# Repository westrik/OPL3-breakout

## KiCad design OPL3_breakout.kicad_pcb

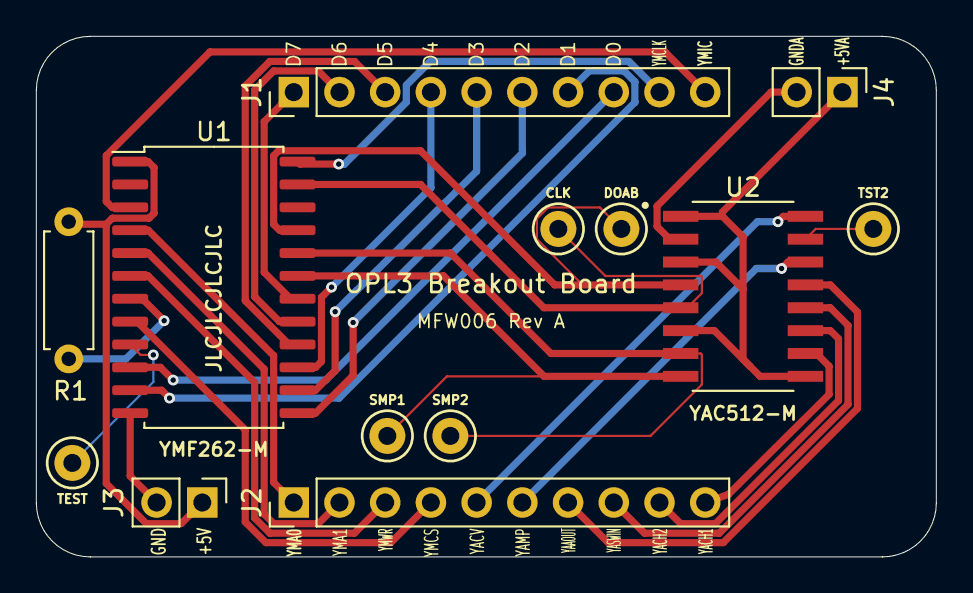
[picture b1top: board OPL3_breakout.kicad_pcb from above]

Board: 4 copper layers, 50.0 x 28.9 mm, 13 parts (0 on the bottom side), 31 nets.

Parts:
J1, J2: Conn_01x10; PinHeader_1x10_P2.54mm_Vertical
J3, J4: Conn_01x02; PinHeader_1x02_P2.54mm_Vertical
R1: 10K; R_Axial_DIN0207_L6.3mm_D2.5mm_P7.62mm_Horizontal
TP1: DOAB; TestPoint_Keystone_5000-5004_Miniature
TP2: CLK; TestPoint_Keystone_5000-5004_Miniature
TP3: TST2; TestPoint_Keystone_5000-5004_Miniature
TP4: TEST; TestPoint_Keystone_5000-5004_Miniature
TP5: SMP2; TestPoint_Keystone_5000-5004_Miniature
TP6: SMP1; TestPoint_Keystone_5000-5004_Miniature
U1: YMF262-M; SOP-24_7.5x15.4mm_P1.27mm
U2: YAC512-M; SOP127P780X200-16N

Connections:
+5V: J3.1, R1.1, U1.1
+5VA: J4.1, U2.1, U2.3, U2.6, U2.9
/D0: J1.8, U1.10
/D1: J1.7, U1.11
/D2: J1.6, U1.13
/D3: J1.5, U1.14
/D4: J1.4, U1.15
/D5: J1.3, U1.16
/D6: J1.2, U1.17
/D7: J1.1, U1.18
/YA_AOUT: J2.7, U2.13
/YA_CH1: J2.10, U2.10
/YA_CH2: J2.9, U2.11
/YA_CV: J2.5, U2.16
/YA_MP: J2.6, U2.14
/YA_SWIN: J2.8, U2.12
/YM_A0: J2.1, U1.4
/YM_A1: J2.2, U1.5
/YM_CLK: J1.9, U1.24
/YM_CS: J2.4, U1.8
/YM_IC: J1.10, U1.3
/YM_WR: J2.3, U1.6
GND: J3.2, U1.12
GNDA: J4.2, U2.2
unnamed: R1.2, U1.7
unnamed: TP1.1, U1.21, U2.4
unnamed: TP2.1, U1.23, U2.5
unnamed: TP3.1, U2.15
unnamed: TP4.1, U1.9
unnamed: TP5.1, U1.20, U2.7
unnamed: TP6.1, U1.19, U2.8

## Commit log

2020-12-22 add test points
